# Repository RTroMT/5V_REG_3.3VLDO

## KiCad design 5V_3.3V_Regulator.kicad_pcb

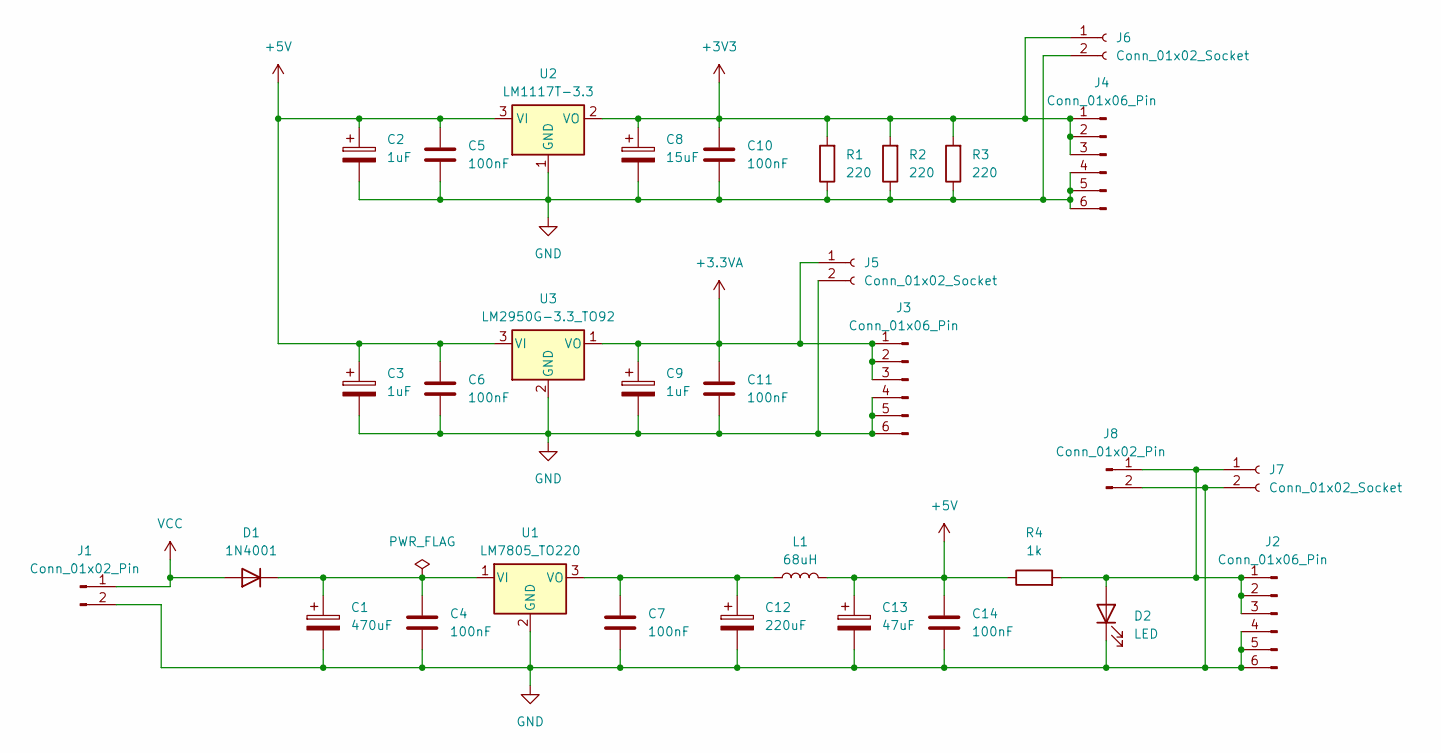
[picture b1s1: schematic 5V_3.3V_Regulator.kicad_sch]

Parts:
C1: 470uF; CP_Radial_D10.0mm_P5.00mm
C2, C3, C9: 1uF; CP_Radial_D5.0mm_P2.00mm
C4, C5, C6, C7, C10, C11, C14: 100nF; C_Disc_D3.4mm_W2.1mm_P2.50mm
C8: 15uF; CP_Radial_D8.0mm_P2.50mm
C12: 220uF; CP_Radial_D6.3mm_P2.50mm
C13: 47uF; CP_Radial_D13.0mm_P5.00mm
D1: 1N4001; D_DO-41_SOD81_P10.16mm_Horizontal
D2: LED; LED_D3.0mm
J1, J8: Conn_01x02_Pin; JST_VH_B2P-VH-B_1x02_P3.96mm_Vertical
J2, J3, J4: Conn_01x06_Pin; PinHeader_1x06_P2.54mm_Vertical
J5, J6, J7: Conn_01x02_Socket; JST_XH_B2B-XH-A_1x02_P2.50mm_Vertical
L1: 68uH; L_Toroid_Vertical_L14.0mm_W6.3mm_P4.57mm_Pulse_A
R1, R2, R3: 220; R_Axial_DIN0204_L3.6mm_D1.6mm_P7.62mm_Horizontal
R4: 1k
U1: LM7805_TO220; TO-220-3_Vertical
U2: LM1117T-3.3; TO-220-3_Vertical
U3: LM2950G-3.3_TO92; TO-92_Inline

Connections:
+3.3VA: C9.1, C11.1, J3.1, J3.2, J3.3, J5.1, U3.1 (VO)
+3V3: C8.1, C10.1, J4.1, J4.2, J4.3, J6.1, R1.2, R2.2, R3.2, U2.2 (VO)
+5V: C2.1, C3.1, C5.1, C6.1, C13.1, C14.1, L1.2, R4.1, U2.3 (VI), U3.3 (VI)
GND: C1.2, C2.2, C3.2, C4.2, C5.2, C6.2, C7.2, C8.2, C9.2, C10.2, C11.2, C12.2, C13.2, C14.2, D2.1 (K), J1.2, J2.4, J2.5, J2.6, J3.4, J3.5, J3.6, J4.4, J4.5, J4.6, J5.2, J6.2, J7.2, J8.2, R1.1, R2.1, R3.1, U1.2 (GND), U2.1 (GND), U3.2 (GND)
unnamed: C1.1, C4.1, D1.1 (K), U1.1 (VI)
unnamed: D2.2 (A), J2.1, J2.2, J2.3, J7.1, J8.1, R4.2
unnamed: C7.1, C12.1, L1.1, U1.3 (VO)
VCC: D1.2 (A), J1.1

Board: 2 copper layers, 31 parts (0 on the bottom side), 8 nets, no tracks yet.

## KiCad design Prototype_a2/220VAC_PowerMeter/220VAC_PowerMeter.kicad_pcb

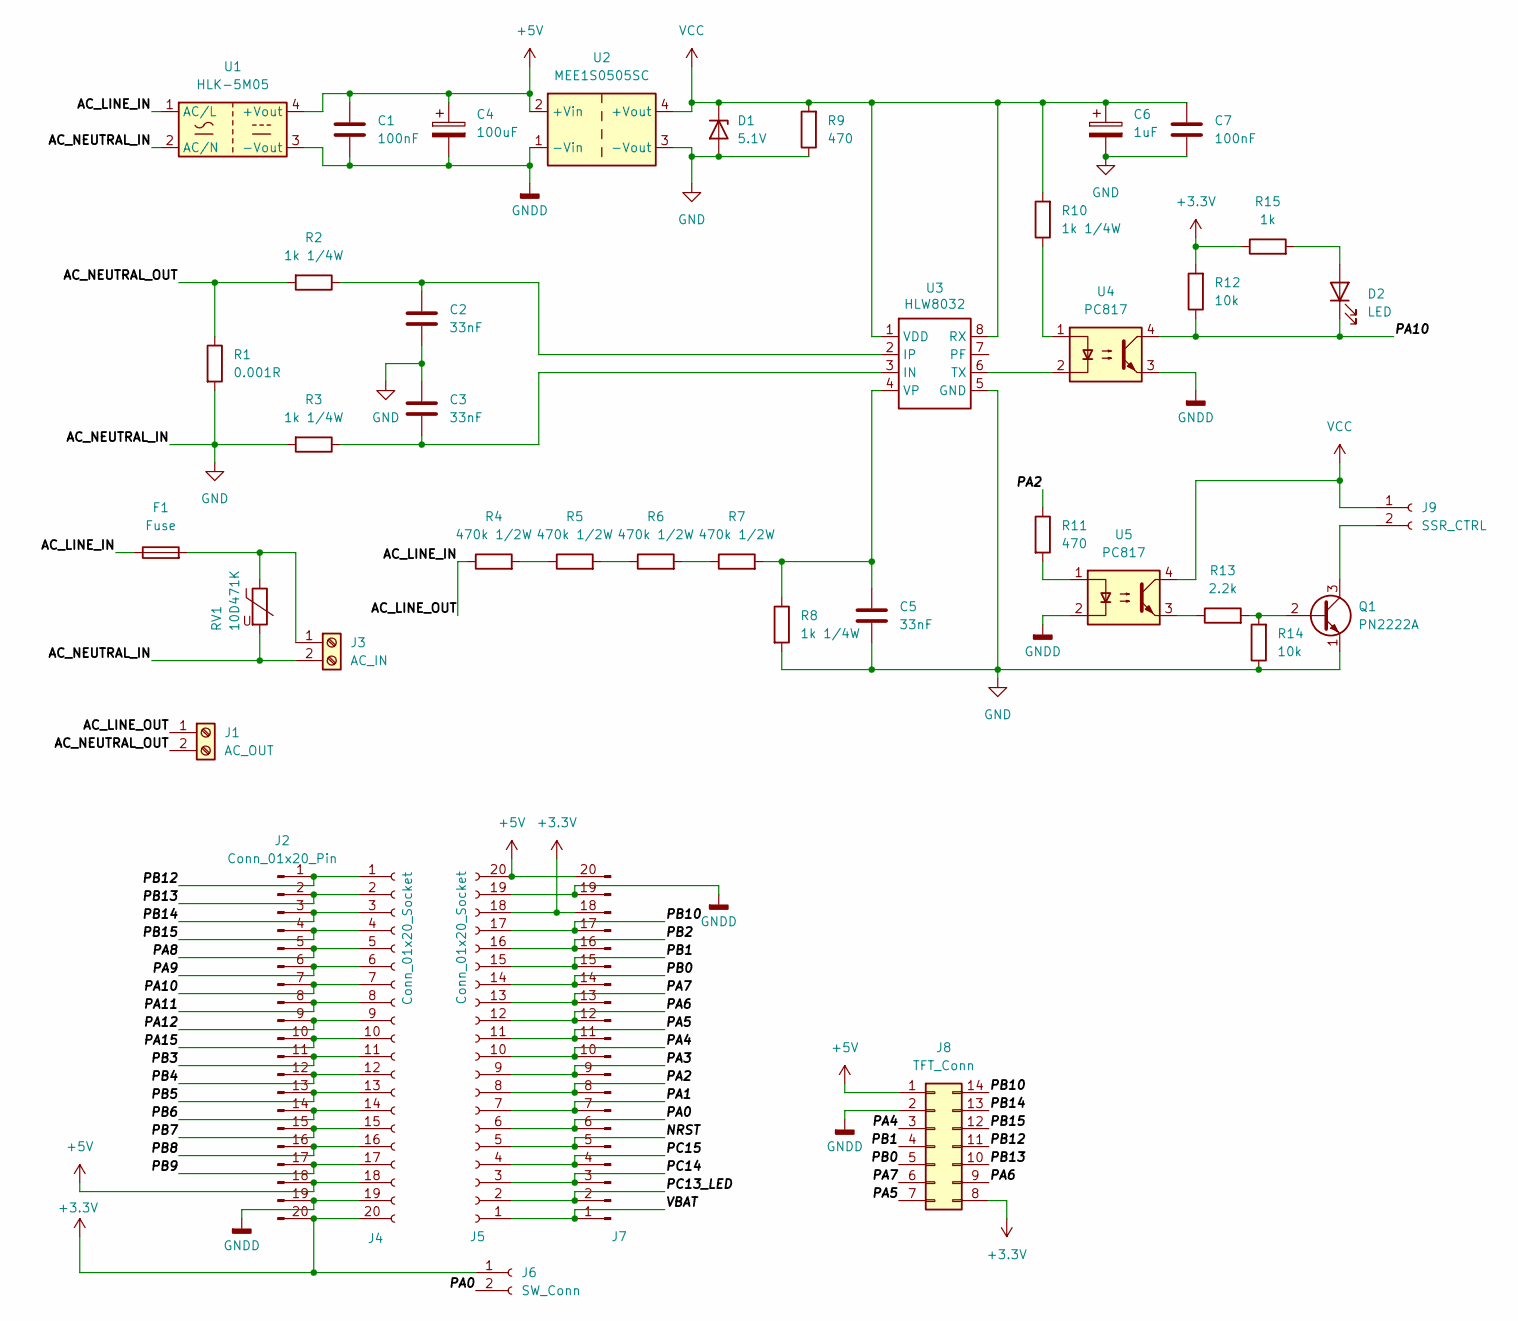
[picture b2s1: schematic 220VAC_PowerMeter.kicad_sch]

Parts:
C1, C7: 100nF; C_0805_2012Metric_Pad1.18x1.45mm_HandSolder
C2, C3: 33nF; C_Rect_L11.0mm_W5.1mm_P10.00mm_MKT
C4: 100uF; CP_Radial_D5.0mm_P2.50mm
C5: 33nF; C_0805_2012Metric_Pad1.18x1.45mm_HandSolder
C6: 1uF; CP_Radial_D5.0mm_P2.00mm
D1: 5.1V; D_DO-41_SOD81_P3.81mm_Vertical_AnodeUp
D2: LED; LED_D3.0mm
F1: Fuse; Fuseholder_Clip-5x20mm_Keystone_3512_Inline_P23.62x7.27mm_D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
J1: AC_OUT; TerminalBlock_Ningbo-Kagnex_HB9500_1x02_P9.5mm
J2: Conn_01x20_Pin; PinHeader_1x20_P2.54mm_Vertical
J3: AC_IN; TerminalBlock_Ningbo-Kagnex_HB9500_1x02_P9.5mm
J4, J5: Conn_01x20_Socket; PinSocket_1x20_P2.54mm_Vertical
J6: SW_Conn; JST_XH_B2B-XH-A_1x02_P2.50mm_Vertical
J7: PinHeader_1x20_P2.54mm_Vertical
J8: TFT_Conn; IDC-Header_2x07_P2.54mm_Vertical
J9: SSR_CTRL; JST_XH_B2B-XH-A_1x02_P2.50mm_Vertical
Q1: PN2222A; TO-92_Inline
R1: 0.001R; R_Axial_DIN0207_L6.3mm_D2.5mm_P10.16mm_Horizontal
R2, R3, R8, R10: 1k 1/4W; R_Axial_DIN0207_L6.3mm_D2.5mm_P7.62mm_Horizontal
R4, R5, R6, R7: 470k 1/2W; R_Axial_DIN0207_L6.3mm_D2.5mm_P10.16mm_Horizontal
R9, R11: 470; R_Axial_DIN0207_L6.3mm_D2.5mm_P7.62mm_Horizontal
R12, R14: 10k; R_Axial_DIN0207_L6.3mm_D2.5mm_P7.62mm_Horizontal
R13: 2.2k; R_Axial_DIN0207_L6.3mm_D2.5mm_P7.62mm_Horizontal
R15: 1k; R_Axial_DIN0207_L6.3mm_D2.5mm_P7.62mm_Horizontal
RV1: 10D471K; RV_Disc_D9mm_W4mm_P5mm
U1: HLK-5M05; Converter_ACDC_Hi-Link_HLK-5Mxx
U2: MEE1S0505SC; Converter_DCDC_Murata_MEE1SxxxxSC_THT
U3: HLW8032; SOIC-8_3.9x4.9mm_P1.27mm
U4, U5: PC817; DIP-4_W7.62mm_LongPads

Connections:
+3.3V: J2.20, J4.20, J5.18, J6.1, J7.18, J8.8, R12.2, R15.1
+5V: C1.1, C4.1, J2.18, J4.18, J5.20, J7.20, J8.1, U1.4 (+Vout), U2.2 (+Vin)
/AC_LINE_IN: F1.1, J1.1, R4.1, U1.1 (AC/L)
/AC_NEUTRAL_OUT: J1.2, R1.1, R2.2
/NRST: J5.5, J7.5
/PA0: J5.6, J6.2, J7.6
/PA1: J5.7, J7.7
/PA2: J5.8, J7.8, R11.1
/PA3: J5.9, J7.9
/PA4: J5.10, J7.10, J8.3
/PA5: J5.11, J7.11, J8.7
/PA6: J5.12, J7.12, J8.9
/PA7: J5.13, J7.13, J8.6
/PA8: J2.5, J4.5
/PA9: J2.6, J4.6
/PA10: D2.1 (K), J2.7, J4.7, R12.1, U4.4
/PA11: J2.8, J4.8
/PA12: J2.9, J4.9
/PA15: J2.10, J4.10
/PB0: J5.14, J7.14, J8.5
/PB1: J5.15, J7.15, J8.4
/PB2: J5.16, J7.16
/PB3: J2.11, J4.11
/PB4: J2.12, J4.12
/PB5: J2.13, J4.13
/PB6: J2.14, J4.14
/PB7: J2.15, J4.15
/PB8: J2.16, J4.16
/PB9: J2.17, J4.17
/PB10: J5.17, J7.17, J8.14
/PB12: J2.1, J4.1, J8.11
/PB13: J2.2, J4.2, J8.10
/PB14: J2.3, J4.3, J8.13
/PB15: J2.4, J4.4, J8.12
/PC13_LED: J5.2, J7.2
/PC14: J5.3, J7.3
/PC15: J5.4, J7.4
/VBAT: J5.1, J7.1
GND: C2.2, C3.1, C5.2, C6.2, C7.2, D1.2 (A), J3.2, Q1.1 (E), R1.2, R3.2, R8.2, R9.1, R14.1, RV1.2, U1.2 (AC/N), U2.3 (-Vout), U3.5 (GND)
GNDD: C1.2, C4.2, J2.19, J4.19, J5.19, J7.19, J8.2, U1.3 (-Vout), U2.1 (-Vin), U4.3, U5.2
unnamed: D2.2 (A), R15.2
unnamed: F1.2, J3.1, RV1.1
unnamed: J9.2, Q1.3 (C)
unnamed: Q1.2 (B), R13.2, R14.2
unnamed: R4.2, R5.1
unnamed: R5.2, R6.1
unnamed: R6.2, R7.1
unnamed: R10.1, U4.1
unnamed: R11.2, U5.1
unnamed: R13.1, U5.3
unnamed: C3.2, R3.1, U3.3 (IN)
unnamed: C2.1, R2.1, U3.2 (IP)
unnamed: U3.6 (TX), U4.2
unnamed: C5.1, R7.2, R8.1, U3.4 (VP)
VCC: C6.1, C7.1, D1.1 (K), J9.1, R9.2, R10.2, U2.4 (+Vout), U3.1 (VDD), U3.8 (RX), U5.4

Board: 2 copper layers, 41 parts (0 on the bottom side), 55 nets, no tracks yet.
